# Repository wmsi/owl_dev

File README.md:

## Welcome to the WMSI Owl Kit Development repository!

Here you can find every sketch ever used on an Owl prototype, as well as some circuit diagrams and files for manufacturing. If you're brand new to the Owls, you'll probably be better off starting with our Comprehensive Owl Guide, which can be found at this link: https://goo.gl/V9kGfm

### examples/
If you are looking for example code for a specific Owl application, <b>check out the examples folder.</b> Most of the names in this folder should be self-explanatory, but if you're confused about a particular application look it up in the guide above.

The code in this folder is by far the best-commented of any in this repository, but once you work through some examples you should be able to navigate the messier prototype code without too many issues.

You can also check out [this guide](https://docs.google.com/document/d/1MRcjBNnCVSWXaH-lBgTyRSfC4LLxEa_yDphGgFJk0CI) on a basic game using the Owls.

### Fritzing/, Eagle/
In the Fritzing and Eagle folders you'll find material related to the Owl circuit as laid out for a breadboard or PCB. The Fritiing files will probably be most useful for reconstructing or understanding how all the parts of the circuit function. Use the Eagle files if you intend to manufacture a PCB or just love staring at circuit diagrams.

### owl projects/
The "owl projects" folder contains sketches for specific educational applications. Each sketch should have a long comment at the top explaining what it was built for and what it does.

### prototype code/
Only go delving into the "prototype code" folder if you have a firm grasp on all the example code. However, if you are struggling with a specific problem, there may be some code in here that solves it :)

However, you may have to peel through layers of old, uncommented, hacked together sketches.

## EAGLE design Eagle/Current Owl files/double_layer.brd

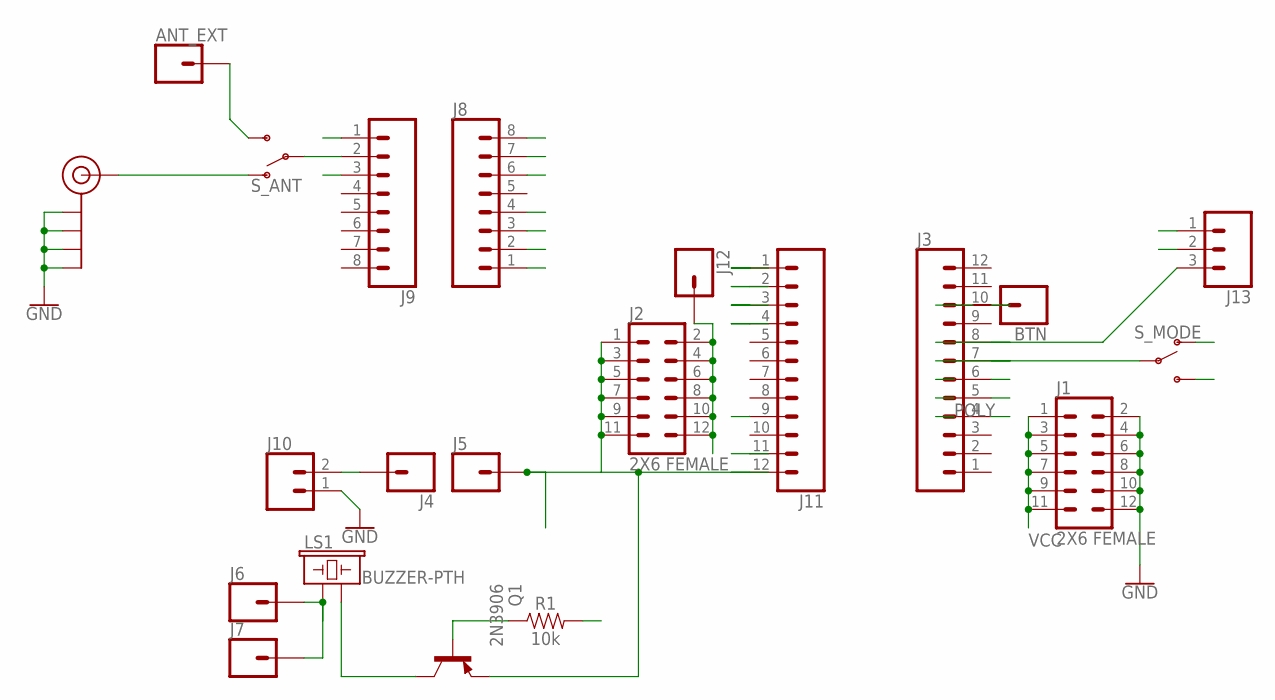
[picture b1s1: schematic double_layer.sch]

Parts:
ANT_EXT: CONN_01; 1X01
BTN: CONN_01; 1X01
J1, J2: 2X6 FEMALE; 2X6
J3, J11: CONN_12; 1X12
J4, J5, J6, J7, J12: CONN_01; 1X01
J8, J9: CONN_08"; 1X08
J10: CONN_02JST-PTH-2; JST-2-PTH
J13: CONN_03JST-PTH; JST-3-PTH
J$1: SMA_EDGE; SMA-EDGE
LS1: BUZZER-PTH; BUZZER-12MM
Q1: 2N3906; TO92
R1: 10k; AXIAL-0.3
S_ANT: SWITCH-SPDT-PTH-11.6X4.0MM; SWITCH_SPDT_PTH_11.6X4.0MM
S_MODE: SWITCH-SPDT-PTH-11.6X4.0MM; SWITCH_SPDT_PTH_11.6X4.0MM

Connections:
7: J3.7, S_MODE.2
8: J3.8
10: BTN.1, J3.10
ANT: J9.2, S_ANT.2
DIO0: J3.5, J8.6
GND: J1.2, J1.4, J1.6, J1.8, J1.10, J1.12, J2.2, J2.4, J2.6, J2.8, J2.10, J2.12, J3.4, J8.7, J9.1, J9.3, J10.1, J11.11, J12.1, J13.2, J$1.GND@0 (GND), J$1.GND@1 (GND), J$1.GND@2 (GND), J$1.GND@3 (GND), S_MODE.3 (S)
MISO: J8.1, J11.3
MOSI: J8.2, J11.2
unnamed: LS1.- (2), Q1.1 (C)
unnamed: Q1.2 (B), R1.P$1 (1)
unnamed: ANT_EXT.1, S_ANT.3 (S)
unnamed: J$1.SIG (SIGNAL), S_ANT.1 (O)
unnamed: J4.1, J10.2
unnamed: J6.1, J7.1, LS1.+ (1)
NSS: J8.4, J11.1
RAW: J2.1, J2.3, J2.5, J2.7, J2.9, J2.11, J5.1, J11.12, Q1.3 (E)
SCK: J8.3, J11.4
SPKR: J3.6, R1.P$2 (2)
VCC: J1.1, J1.3, J1.5, J1.7, J1.9, J1.11, J8.8, J11.9, J13.1, S_MODE.1 (O)

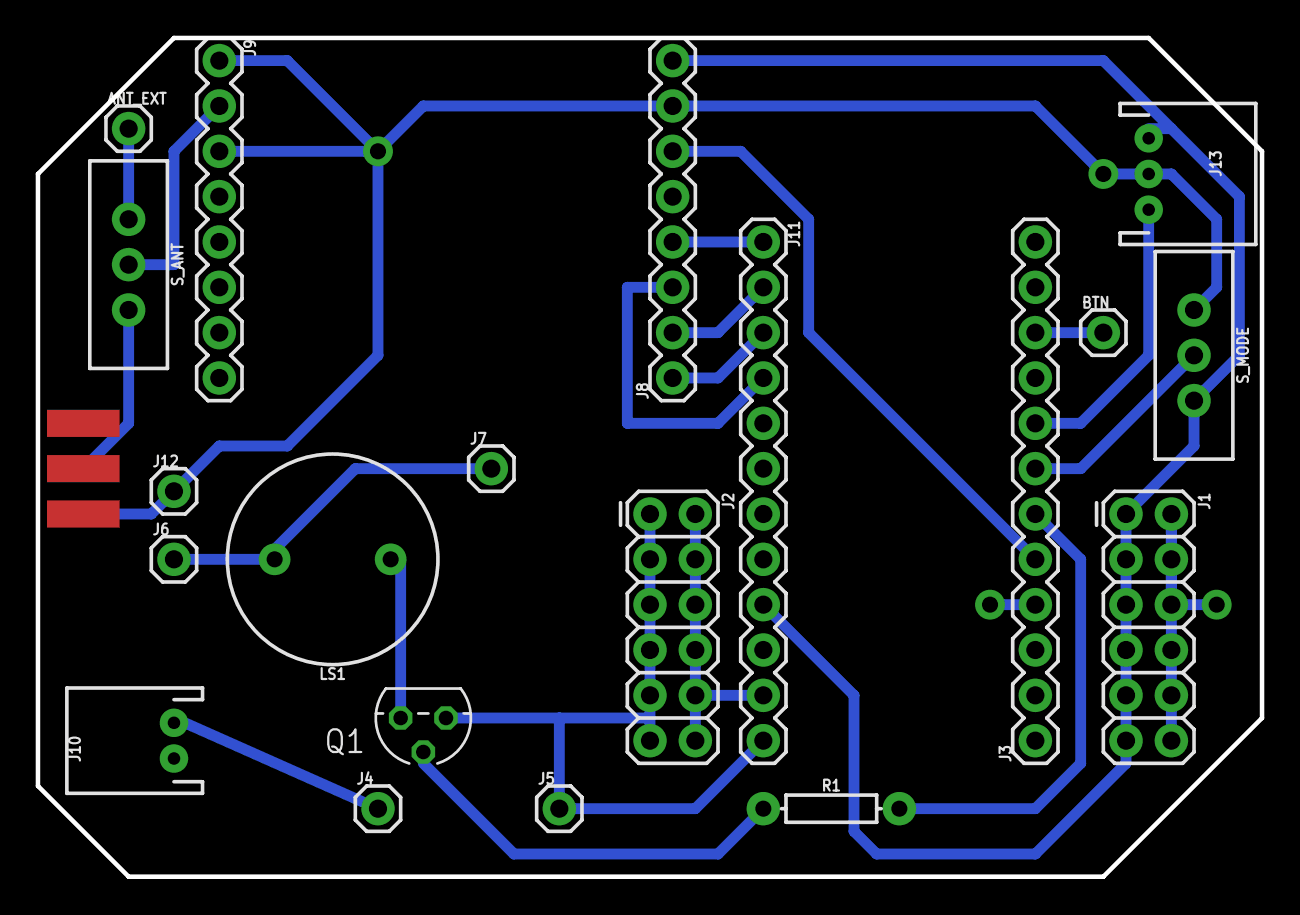
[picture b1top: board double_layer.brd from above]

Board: 2 copper layers, 68.6 x 47.0 mm, 21 parts (0 on the bottom side), 18 nets.

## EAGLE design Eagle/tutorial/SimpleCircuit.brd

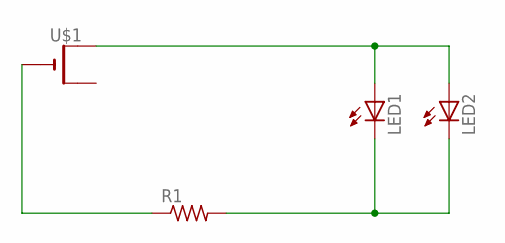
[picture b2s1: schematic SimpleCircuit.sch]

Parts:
LED1, LED2: LED5MM
R1: R-US_0309/12; 0309/12
U$1: CR2032THM; CR2032-THRU

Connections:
unnamed: LED1.A, LED2.A, U$1.+1 (+)
unnamed: LED1.K (C), LED2.K (C), R1.2
unnamed: R1.1, U$1.-

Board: 2 copper layers, 4 parts (0 on the bottom side), 3 nets, no tracks yet.

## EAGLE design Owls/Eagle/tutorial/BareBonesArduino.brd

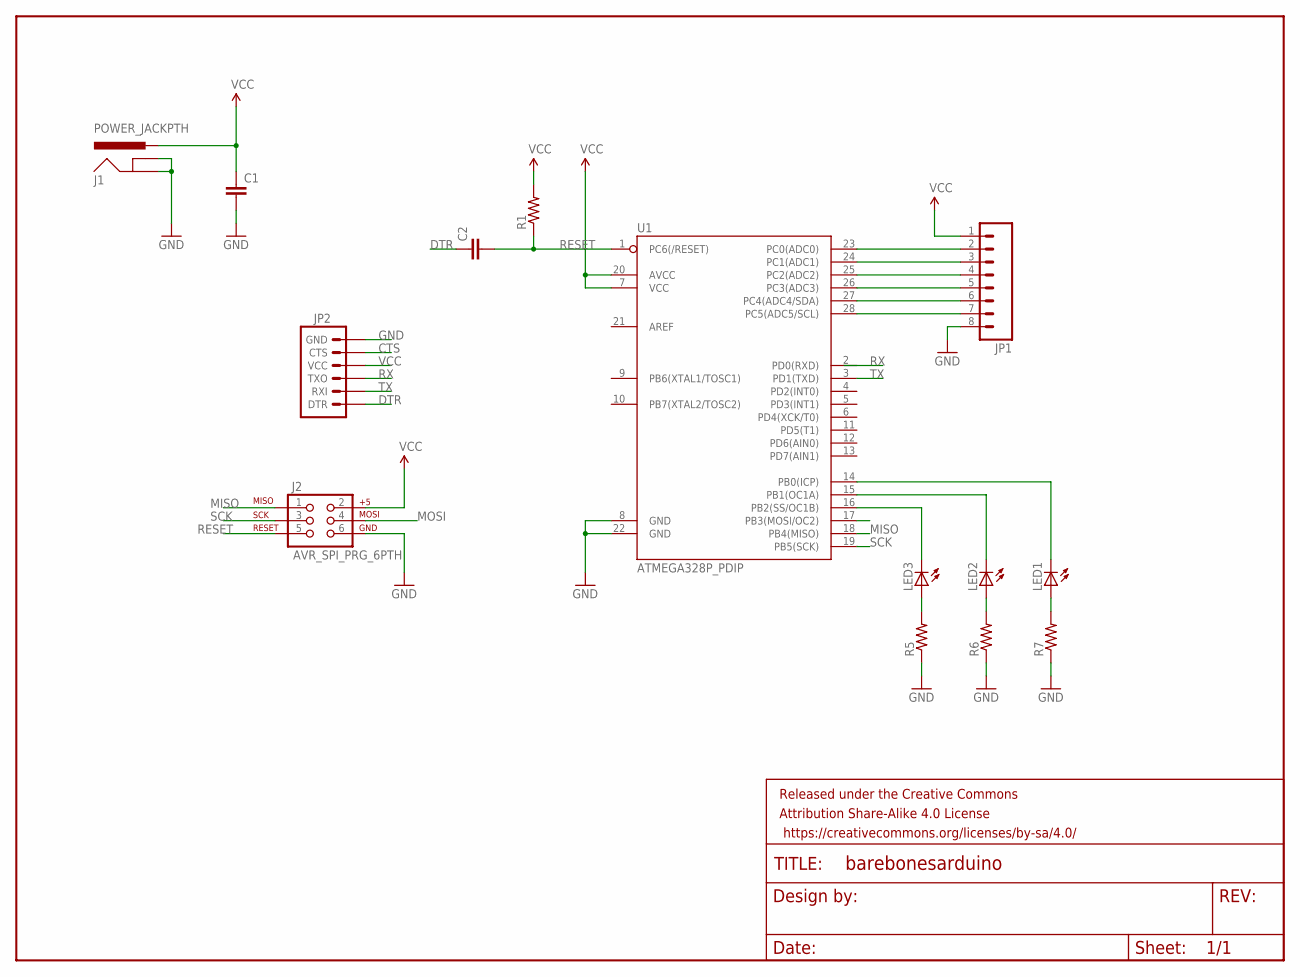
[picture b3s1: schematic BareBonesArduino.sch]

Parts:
C1, C2: CAPPTH; CAP-PTH-SMALL
FRAME1: FRAME-LETTER; CREATIVE_COMMONS
J1: POWER_JACKPTH; POWER_JACK_PTH
J2: AVR_SPI_PRG_6PTH; 2X3
JP1: M081X08; 1X08
JP2: ARDUINO_SERIAL_PROGRAMPTH; 1X06
LED1, LED2, LED3: LED5MM
R1, R5, R6, R7: RESISTORPTH-1/4W; AXIAL-0.4
U1: ATMEGA328P_PDIP; DIL28-3

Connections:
CTS: JP2.5 (CTS)
DTR: C2.1, JP2.1 (DTR)
GND: C1.2, J1.GND, J1.GNDBREAK, J2.6, JP1.8, JP2.6 (GND), R5.P$1 (1), R6.P$1 (1), R7.P$1 (1), U1.8 (GND), U1.22 (GND)
MISO: J2.1, U1.18 (PB4(MISO))
MOSI: J2.4, LED3.K (C), U1.16 (PB2(SS/OC1B)), U1.17 (PB3(MOSI/OC2))
unnamed: JP1.4, U1.25 (PC2(ADC2))
unnamed: LED2.A, R6.P$2 (2)
unnamed: JP1.2, U1.23 (PC0(ADC0))
unnamed: JP1.3, U1.24 (PC1(ADC1))
unnamed: JP1.5, U1.26 (PC3(ADC3))
unnamed: JP1.7, U1.28 (PC5(ADC5/SCL))
unnamed: JP1.6, U1.27 (PC4(ADC4/SDA))
unnamed: LED2.K (C), U1.15 (PB1(OC1A))
unnamed: LED1.K (C), U1.14 (PB0(ICP))
unnamed: LED3.A, R5.P$2 (2)
unnamed: LED1.A, R7.P$2 (2)
RESET: C2.2, J2.5, R1.P$1 (1), U1.1 (PC6(/RESET))
RX: JP2.3 (TXO)
SCK: J2.3, U1.19 (PB5(SCK))
TX: JP2.2 (RXI), U1.3 (PD1(TXD))
VCC: C1.1, J1.PWR, J2.2, JP1.1, JP2.4 (VCC), R1.P$2 (2), U1.7 (VCC), U1.20 (AVCC)

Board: 2 copper layers, 15 parts (0 on the bottom side), 19 nets, no tracks yet.

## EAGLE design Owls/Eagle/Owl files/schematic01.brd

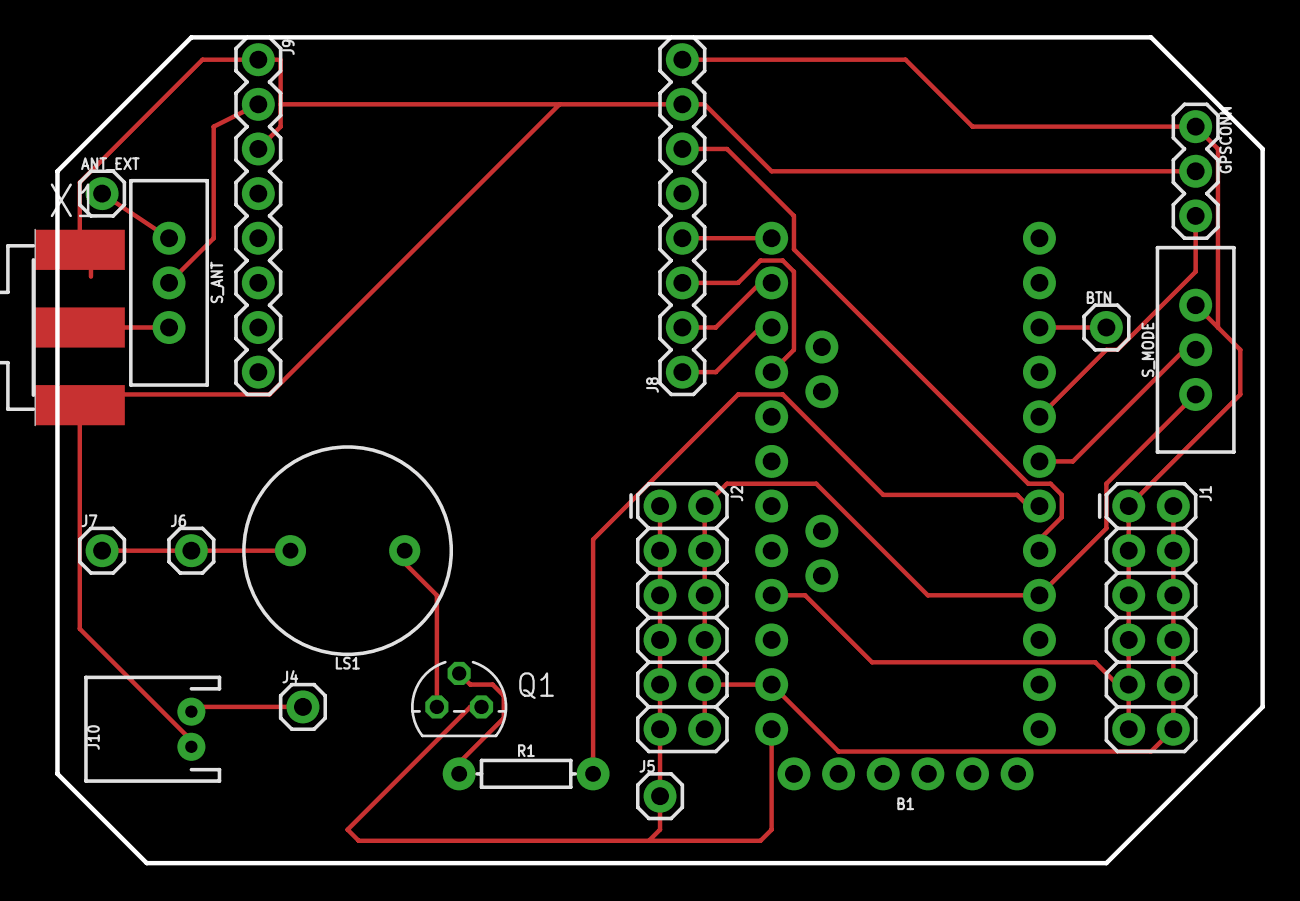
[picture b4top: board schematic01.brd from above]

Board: 2 copper layers, 69.7 x 47.0 mm, 20 parts (0 on the bottom side), 19 nets.

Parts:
ANT_EXT: 1X01
B1: ARDUINO_PRO_MINI
BTN: 1X01
FRAME1: FRAME-LETTER; CREATIVE_COMMONS
GPSCONN: 1X03
J1, J2: 2X6 FEMALE; 2X6
J4, J5, J6, J7: 1X01
J8, J9: 1X08
J10: JST-2-PTH
LS1: BUZZER-PTH; BUZZER-12MM
Q1: 2N3906; TO92
R1: 10k; AXIAL-0.3
S_ANT: SWITCH_SPDT_PTH_11.6X4.0MM
S_MODE: SWITCH_SPDT_PTH_11.6X4.0MM
X1: SMA-142-0701-851/861; J502-ND-142-0701-851/861

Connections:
ANT: J9.2, S_ANT.2
DIO0: B1.5, J8.6
MISO: B1.15, J8.1
MOSI: B1.14, J8.2
unnamed: B1.8, GPSCONN.3
unnamed: B1.7, S_MODE.2
unnamed: LS1.-, Q1.3
unnamed: Q1.2, R1.P$1
unnamed: ANT_EXT.1, S_ANT.3
unnamed: S_ANT.1, X1.1
unnamed: B1.10, BTN.1
unnamed: J4.1, J10.2
unnamed: J6.1, J7.1, LS1.+
NSS: B1.13, J8.4
POLY: B1.4, B1.23, GPSCONN.2, J1.2, J1.4, J1.6, J1.8, J1.10, J1.12, J2.2, J2.4, J2.6, J2.8, J2.10, J2.12, J8.7, J9.1, J9.3, J10.1, S_MODE.3, X1.G@1, X1.G@2, X1.G@3, X1.G@4
RAW: B1.24, J2.1, J2.3, J2.5, J2.7, J2.9, J2.11, J5.1, Q1.1
SCK: B1.16, J8.3
SPKR: B1.6, R1.P$2
VCC: B1.21, GPSCONN.1, J1.1, J1.3, J1.5, J1.7, J1.9, J1.11, J8.8, S_MODE.1

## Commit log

2017-01-12 test
2017-01-12 switch mode sketches
2017-01-19 update for hackandhang:
2017-01-26 pushing software for profile owls
2017-01-26 added readme to profile folder
2017-01-27 updated BlinkSS()
2017-02-15 updated readme and folder name
2017-02-15 removed old folder
2017-04-03 reorganized code, added examples folder
2017-04-07 added sensor_read.ino
2017-04-07 added ticking_timer.ino
2017-04-11 adding woodland_gps_demo.ino
2017-04-12 added simple transmit/ receive examples for both microprocessors
2017-04-12 did some reorganizing, added eagle stuff
2017-04-12 reorganized and added Feather sensor example
2017-04-18 changed folders around
2017-04-19 added README
2017-04-25 updated a readme
2017-04-28 updated eagle files
2017-05-04 added martian draft code
2017-08-02 Reorganize and clean up docs

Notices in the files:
parts and their libraries:
SparkFun-Connectors: Licensing: Creative Commons ShareAlike 4.0 International - https://creativecommons.org/licenses/by-sa/4.0
SparkFun-Aesthetics: Released under the Creative Commons Attribution Share-Alike 4.0 License
SparkFun-Aesthetics: https://creativecommons.org/licenses/by-sa/4.0
